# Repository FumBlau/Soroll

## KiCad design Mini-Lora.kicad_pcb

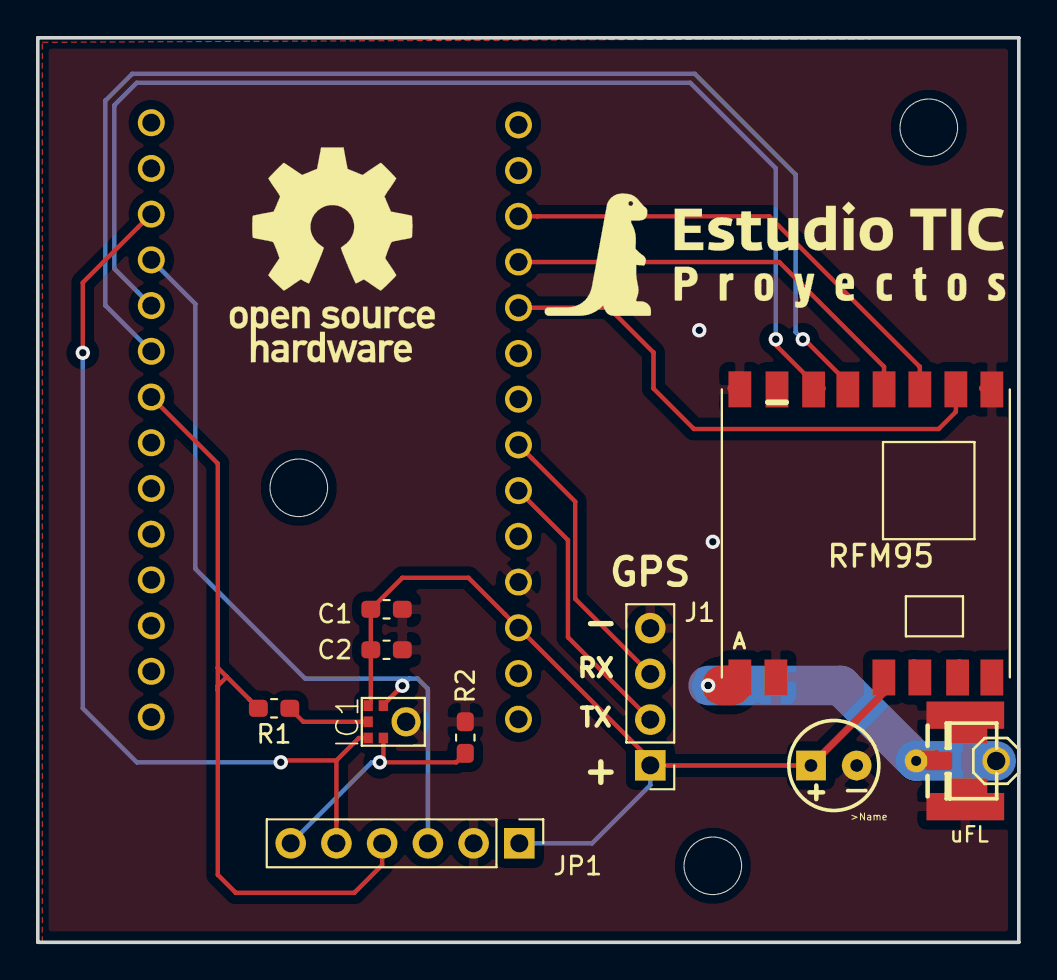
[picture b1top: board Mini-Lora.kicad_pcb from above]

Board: 2 copper layers, 54.5 x 50.2 mm, 12 parts (0 on the bottom side), 15 nets.

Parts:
C1: 220pF; C_0603_1608Metric_Pad1.05x0.95mm_HandSolder
C2: 1uF; C_0603_1608Metric_Pad1.05x0.95mm_HandSolder
C4: 10u; CPOL-RADIAL-10UF-25V
IC1: MIC_I2S_SPH0645; SPH0645LM4H
J1: Conn_01x04_Female; PinHeader_1x04_P2.54mm_Vertical
J$2: ANTENNATINY; SMA_UFL_PAD_TINY
JP1: HEADER-1X6; PinHeader_1x06_P2.54mm_Vertical
JP3: PINHD-1X1; 1X01
R1: 68; R_0603_1608Metric_Pad1.05x0.95mm_HandSolder
R2: 10K; R_0603_1608Metric_Pad1.05x0.95mm_HandSolder
U2: MKR_ZERO; MKRFox1200
U$5: RFM95

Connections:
+3V3: C1.1, C2.1, C4.1, IC1.5, J1.1, JP1.1, U2.26, U$5.VDD
/ANT: J$2.ANT1, J$2.ANT2, J$2.ANT3, JP3.1, U$5.ANT
/ICS_SCK: IC1.4, JP1.3, U2.11
/MISO: U2.19, U$5.MISO
/MOSI: U2.17, U$5.MOSI
/RESET: U2.10, U$5.RST
/RX: J1.3, U2.22
/SCK: U2.18, U$5.SCK
/SD: JP1.4, R1.2, U2.8
/SS: U2.9, U$5.NSS
/Select: IC1.2, JP1.6, R2.1
/TX: J1.2, U2.23
/WS: IC1.1, JP1.5, U2.12
GND: C1.2, C2.2, C4.2, IC1.3, J1.4, J$2.GND1, J$2.GND2, J$2.GND3, J$2.GND4, JP1.2, R2.2, U2.25, U$5.GND, U$5.GND1, U$5.GND2
unnamed: IC1.6, R1.1

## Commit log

2019-05-22 - V1 de PCB
2019-05-29 - se rehacen los gerbers para pedir
